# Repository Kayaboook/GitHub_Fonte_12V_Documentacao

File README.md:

# Fonte de Alimentação Linear de 12 V DC

Projeto académico de uma fonte de alimentação linear, desenvolvido em KiCad no âmbito do TP1 de Sistemas Embebidos, ano letivo 2026/2027.

## Estado do projeto

O desenho da PCB e a visualização 3D foram apresentados pelo autor como concluídos. Esta versão do repositório é de documentação do projeto CAD: não constitui uma versão validada para fabrico ou utilização.

- PCB: 90 × 60 mm, duas camadas de cobre.
- Montagem mista: componentes THT e SMD.
- Saída nominal de projeto: 12 V DC.
- Fabrico, montagem e ensaios: não documentados.
- Resultados finais de ERC e DRC: não disponibilizados neste pacote.

## Objetivo

Desenvolver o esquema elétrico e uma placa de circuito impresso para uma fonte regulada de 12 V DC, aplicando retificação em ponte, filtragem capacitiva e regulação linear com LM7812.

## Funcionamento

Percurso funcional previsto:

```text
Entrada AC isolada → proteção → ponte retificadora → filtragem
                                                   ↓
                                        regulação LM7812
                                                   ↓
                                     comando ON/OFF → saída
```

Quatro díodos 1N4007 realizam a retificação. Um condensador eletrolítico de 470 µF participa na filtragem, e o projeto inclui dois condensadores cerâmicos de 100 nF. O LM7812 fornece a regulação nominal de 12 V. Um LED com resistência em série indica o estado da saída. A ligação efetiva do fusível, interruptor e indicador deve ser confirmada no esquema final.

## Características

| Parâmetro | Descrição |
|---|---|
| Topologia | Fonte linear com ponte retificadora |
| Saída nominal | 12 V DC |
| Corrente contínua de saída | Por validar |
| Gama admissível de entrada | Por validar |
| Regulador | LM7812, TO-220 vertical |
| PCB | 90 × 60 mm, duas camadas |
| Entrada | Jack; referência selecionada 4300.0104 |
| Saída | Phoenix Contact GMSTBA, 1×02, P7,62 mm, horizontal |
| Comando | Interruptor deslizante SPDT PCM12 |
| Fixação | Quatro furos de canto não metalizados |
| Ferramenta de desenvolvimento | KiCad; versão não registada |

## Componentes e footprints

| Referência | Qtd. | Componente | Footprint atribuído / identificado |
|---|---:|---|---|
| D1–D4 | 4 | 1N4007 | `Diode_THT:D_DO-41_SOD81_P7.62mm_Horizontal` |
| C1 | 1 | 470 µF; tensão nominal a rever | `Capacitor_THT:CP_Radial_D6.3mm_P2.50mm` |
| C3, C4 | 2 | 100 nF, cerâmico | `Capacitor_SMD:C_1206_3216Metric` |
| IC2 | 1 | LM7812 | `Package_TO_SOT_THT:TO-220-3_Vertical` |
| R1 | 1 | 4,7 kΩ | `Resistor_SMD:R_0603_1608Metric` |
| D5 | 1 | LED | `LED_SMD:LED_0805_2012Metric` |
| J1 | 1 | Jack 4300.0104 | `Samacsys:43000104` |
| J2 | 1 | Phoenix Contact GMSTBA | GMSTBA 2,5/2-G-7,62; confirmar nome integral no projeto |
| SW1 | 1 | Interruptor SPDT | `Button_Switch_SMD:SW_SPDT_PCM12` |
| F1 | 1 | Fusível e suporte 5 × 20 mm | Suporte Bulgin FX0457; confirmar nome integral |
| H1 | 1 | Dissipador SK104, 25,4 mm | `Samacsys:SK104254STCTO220` |

A BOM fornecida é preliminar e foi transcrita da lista apresentada, não exportada dos ficheiros CAD. Referências comerciais, tolerâncias, potências, calibre do fusível e modelos 3D devem ser confirmados antes de encomendar componentes.

## Mecânica

Os centros dos furos foram propostos a 5 mm das bordas. Para o contorno apresentado, de (94,30; 59,31) mm a (184,30; 119,31) mm:

| Furo | X (mm) | Y (mm) |
|---|---:|---:|
| Superior esquerdo | 99,30 | 64,31 |
| Superior direito | 179,30 | 64,31 |
| Inferior esquerdo | 99,30 | 114,31 |
| Inferior direito | 179,30 | 114,31 |

Estas coordenadas descrevem a proposta de posicionamento; confirmar no ficheiro PCB final. Para parafusos M3 foi proposto o footprint não metalizado `MountingHole:MountingHole_3.2mm_M3`.

## Requisitos do trabalho

O enunciado exige duas camadas de cobre, planos de massa em TOP e BOT com clearance de 0,5 mm, identificação em serigrafia e furos não metalizados nos cantos. A lista de entregáveis inclui esquema PDF, visualização 3D, BOM e ficheiros Gerber com furação metalizada e não metalizada.

A implementação destes requisitos deve ser verificada no projeto final. O enunciado designa o encapsulamento dos díodos como SOD68; o footprint selecionado usa a designação DO-41/SOD81. Esta diferença deve ser esclarecida antes do fabrico.

## Segurança e pontos críticos

- Alimentar apenas por uma fonte AC de baixa tensão isolada da rede. Não ligar diretamente a 230 V.
- A serigrafia apresentada indica entrada de 15–25 V AC, mas essa gama não está validada.
- A BOM apresentada inclui C1 de 470 µF / 25 V. Não considerar esta tensão nominal adequada para toda a gama inscrita na serigrafia.
- Rever a tensão máxima após retificação, incluindo tolerância e funcionamento sem carga, antes de escolher C1 e o regulador.
- Confirmar os limites do fabricante e da referência exata do LM7812. Limites absolutos não são condições normais de operação.
- A corrente de saída depende da tensão de entrada, ondulação, retificador, fusível, pistas e dissipação térmica.
- Confirmar o contacto térmico e a montagem do dissipador; o modelo 3D não valida o desempenho térmico.
- Corrigir a serigrafia para corresponder às condições efetivamente validadas.

## Organização

```text
README.md
.gitignore
bom/
  bom_preliminar.csv
docs/
  VALIDACAO.md
  PUBLICACAO.md
  images/             # acrescentar imagens reais
hardware/             # acrescentar projeto KiCad real
fabrication/
  gerbers/            # acrescentar apenas exportações revistas
  drill/              # acrescentar furação PTH e NPTH
```

Não foram criados ficheiros CAD, imagens, Gerbers ou relatórios de ensaio fictícios. As pastas técnicas destinam-se a receber os ficheiros reais do autor.

## Abrir o projeto

Depois de adicionar os ficheiros originais, abrir o `.kicad_pro` no KiCad e confirmar as tabelas de bibliotecas. Incluir símbolos, footprints e modelos 3D personalizados necessários. Usar caminhos relativos ao projeto sempre que possível e verificar ERC e DRC antes de exportar ficheiros de fabrico.

## Contexto académico

- Curso: Licenciatura em Engenharia Eletrotécnica e das Telecomunicações.
- Unidade curricular: Sistemas Embebidos.
- Trabalho: TP1 — Projeto de PCBs com KiCad.
- Ano letivo: 2026/2027.

## Autoria

O identificador associado ao projeto é `Kayaboook`, conforme o endereço inscrito no código da PCB.
## Licença

Não foi atribuída uma licença neste pacote. A disponibilização pública não concede, por si só, uma licença de reutilização. Os autores devem selecionar uma licença adequada e respeitar as licenças das bibliotecas e modelos de terceiros.

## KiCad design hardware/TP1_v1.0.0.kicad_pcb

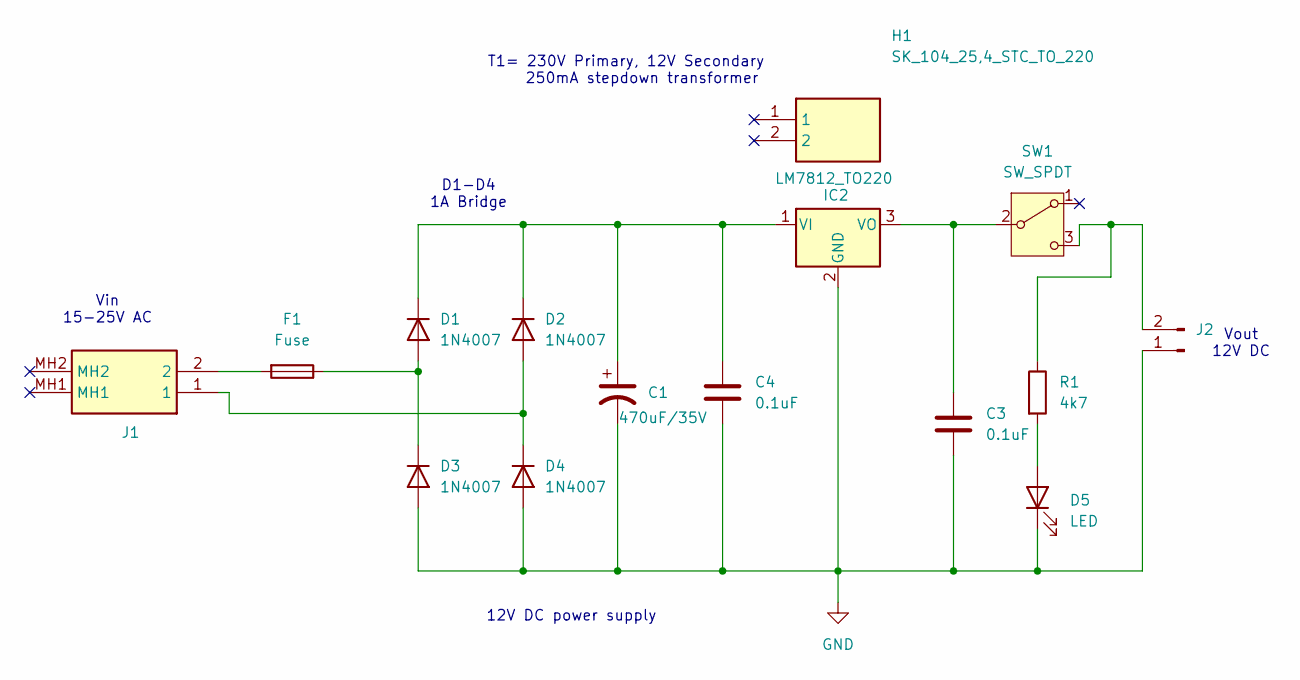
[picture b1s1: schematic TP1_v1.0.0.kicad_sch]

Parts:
C1: 470uF/35V; CP_Radial_D6.3mm_P2.50mm
C3, C4: 0.1uF; C_1206_3216Metric
D1, D2, D3, D4: 1N4007; D_DO-41_SOD81_P7.62mm_Horizontal
D5: LED; LED_0805_2012Metric
F1: Fuse; Fuseholder_Cylinder-5x20mm_Bulgin_FX0457_Horizontal_Closed
H1: SK_104_25,4_STC_TO_220; SK104254STCTO220; Manufacturer_Part_Number SK 104 25,4 STC TO 220
IC2: LM7812_TO220; TO-220-3_Vertical
J1: 4300.0104; 43000104; Manufacturer_Part_Number 4300.0104; Mouser Part Number 693-4300.0104
J2: PhoenixContact_GMSTBA_2,5_2-G-7,62_1x02_P7.62mm_Horizontal
R1: 4k7; R_0603_1608Metric
SW1: SW_SPDT; SW_SPDT_PCM12

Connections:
GND: C1.2, C3.2, C4.2, D3.2 (A), D4.2 (A), D5.1 (K), IC2.2 (GND), J2.1
unnamed: D1.2 (A), D3.1 (K), F1.1
unnamed: C1.1, C4.1, D1.1 (K), D2.1 (K), IC2.1 (VI)
unnamed: D2.2 (A), D4.1 (K), J1.1
unnamed: D5.2 (A), R1.2
unnamed: F1.2, J1.2
unnamed: C3.1, IC2.3 (VO), SW1.2 (B)
unnamed: J2.2, R1.1, SW1.3 (C)

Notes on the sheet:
12V DC power supply
T1= 230V Primary, 12V Secondary 250mA stepdown transformer
Vin 15-25V AC
Vout 12V DC
D1-D4 1A Bridge

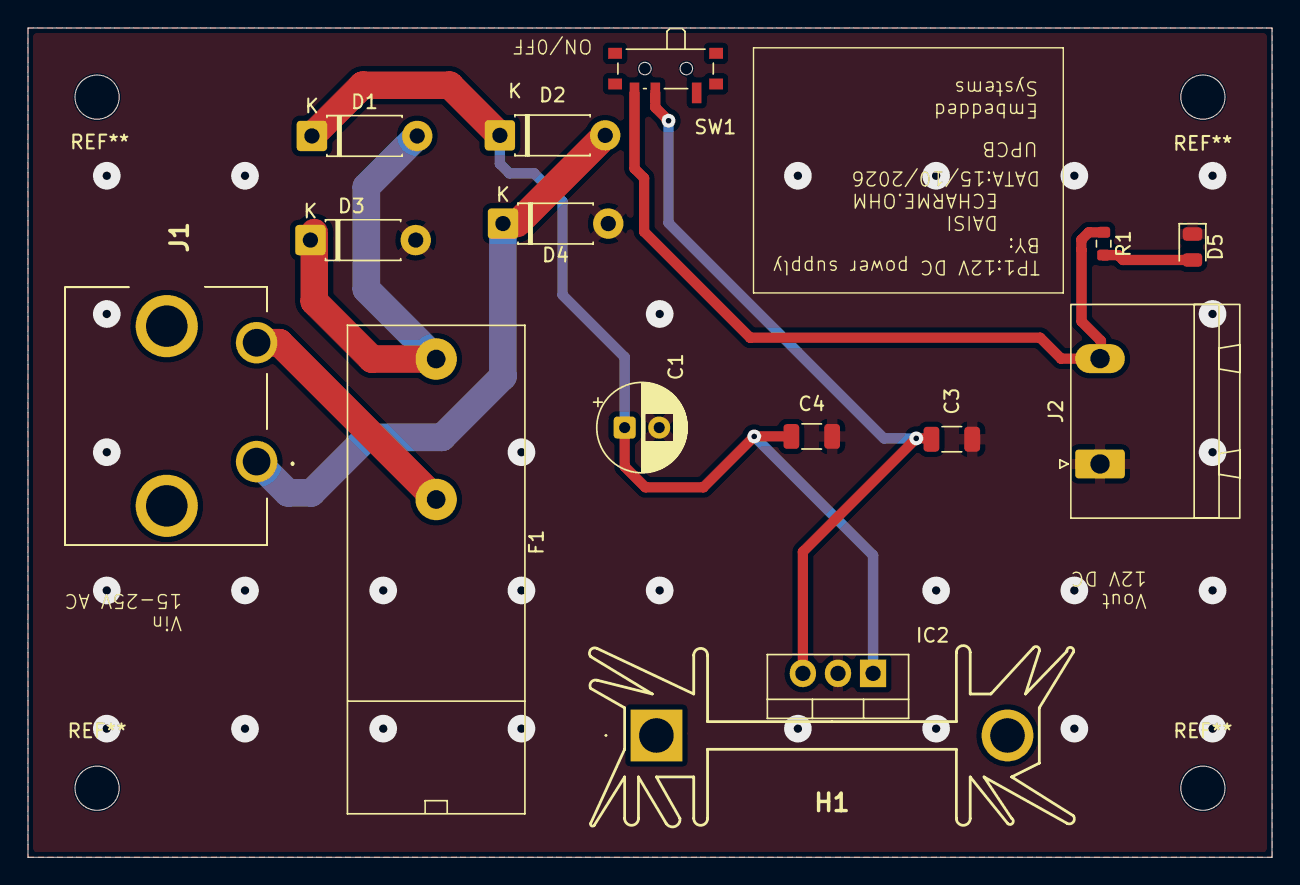
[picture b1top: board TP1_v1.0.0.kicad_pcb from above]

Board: 2 copper layers, 90.0 x 60.0 mm, 15 parts (0 on the bottom side), 8 nets.

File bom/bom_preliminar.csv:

Referencia,Quantidade,Valor,Footprint,Estado
D1-D4,4,1N4007,Diode_THT:D_DO-41_SOD81_P7.62mm_Horizontal,Esclarecer SOD68 no enunciado
C1,1,470uF/25V apresentado,Capacitor_THT:CP_Radial_D6.3mm_P2.50mm,Rever tensao nominal e altura
"C3,C4",2,100nF,Capacitor_SMD:C_1206_3216Metric,Confirmar ceramicos e tensao nominal
IC2,1,LM7812,Package_TO_SOT_THT:TO-220-3_Vertical,Confirmar fabricante e variante
R1,1,4.7k,Resistor_SMD:R_0603_1608Metric,Confirmar potencia e tolerancia
D5,1,LED,LED_SMD:LED_0805_2012Metric,Confirmar cor e polaridade
J1,1,4300.0104,Samacsys:43000104,Confirmar pinagem
J2,1,GMSTBA 1x02 P7.62 horizontal,Confirmar nome completo no CAD,Rever referencia comercial
SW1,1,SW_SPDT,Button_Switch_SMD:SW_SPDT_PCM12,Confirmar ligacao
F1,1,Fuse,Suporte 5x20 Bulgin FX0457 horizontal,Definir calibre; confirmar footprint completo
H1,1,SK104 25.4,Samacsys:SK104254STCTO220,Validar termica e montagem
